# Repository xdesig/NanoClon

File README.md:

# NanoClon V 0.01   

## initial version.
Circuit that has everything you need to assemble your mClon-style robot, 
avoiding having to look for the missing Arduino one from RobotDyn that 
was used in the ShieldClon version.

The components can be SMD or THT, except for the Step-Up circuit/Lipo 
battery charge controller which is SMD,  with 1206 and 0805 components
larger than the usual 0603 and 0402).
You can an option not solder the smd components of the step-up,
and use a power bank by simply soldering the Bat-Vcc selector on the underside.

### [Assembly manual][Man]

#### Deseñado en Estrimia con agarimo.

## Author and license
* Author: [XDeSIG][TWI01]
* License:[CERN Open Hardware Licence Version 2 - Weakly Reciprocal][CERN-OHL-W]

## To buy boards

Developer don't produce boards to sell. Under [_provider_][provider]
directory there are instructions to order yourself.

<!-- links -->
[Man]: https://github.com/xdesig/NanoClon/blob/main/docs/nClon_001_Montaxe.pdf
[tecnoloxia.org]: https://tecnoloxia.org/mclon/que-e-mclon/
[CERN-OHL-W]: https://ohwr.org/cern_ohl_w_v2.pdf
[TWI01]: https://twitter.com/xdesig
[provider]: https://www.pcbway.com/project/shareproject/W50475ASJ144_NanoClon_001_gerber_f511f448.html

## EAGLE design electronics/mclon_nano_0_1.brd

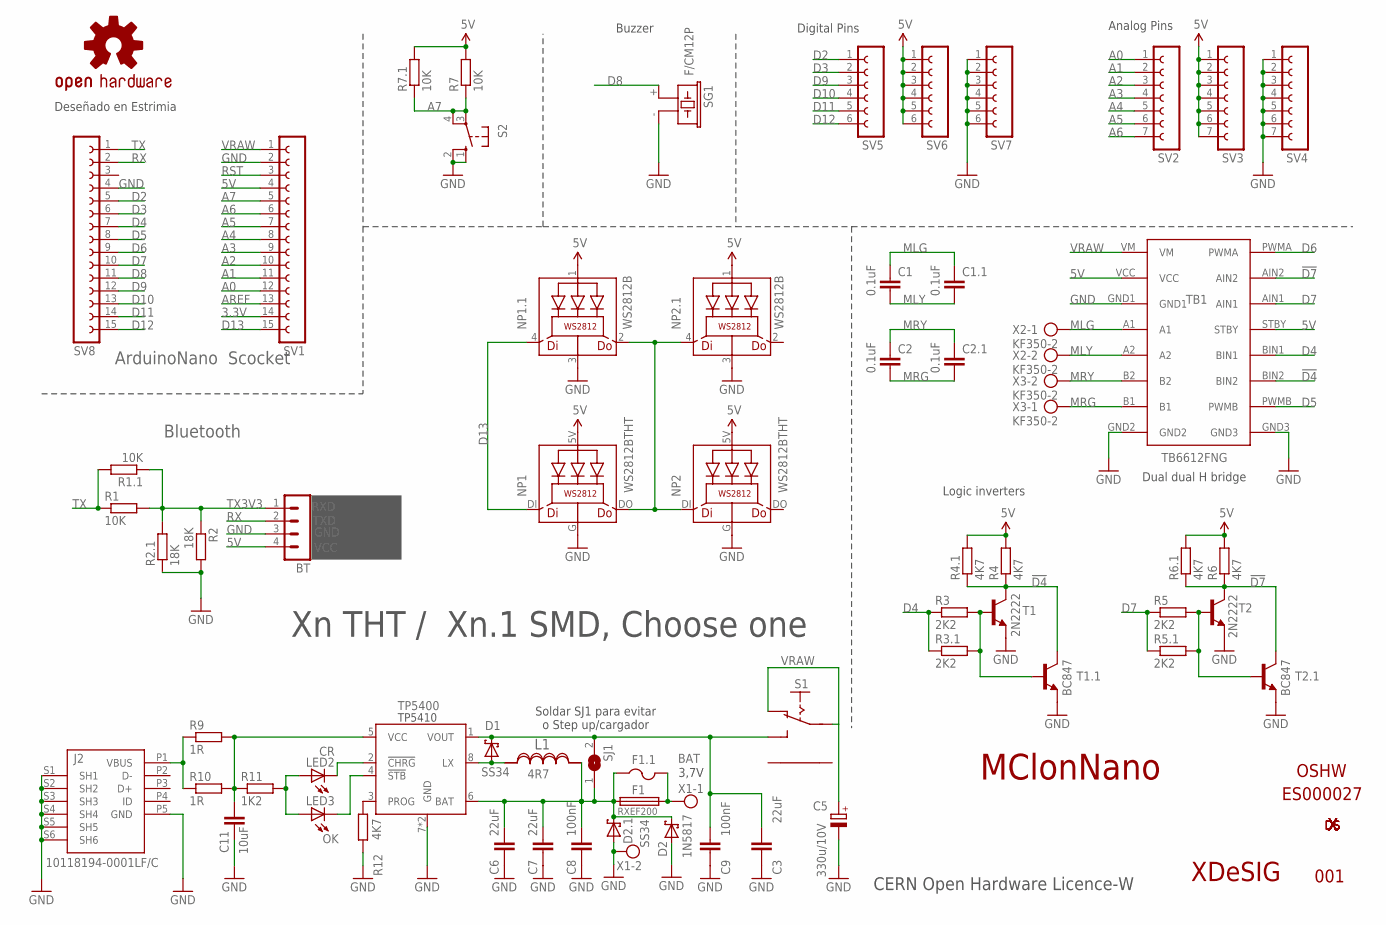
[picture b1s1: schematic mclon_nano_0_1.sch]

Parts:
BT: MA04-1
C1, C2: 0.1uF; C050-024X044
C1.1, C2.1: 0.1uF; C1206
C3, C6, C7: 22uF; C1206
C5: 330u/10V; E2,5-6
C8, C9: 100nF; C1206
C11: 10uF; C1206
D1, D2.1: SS34; DIODE_SMA
D2: 1N5817; DO35-7
F1: RXEF200; TE5
F1.1: MF-NSMF200; 1812
J2: 10118194-0001LF/C; SMARTPRJ_CON2_USB_MICRO_B_AT
L1: 4R7; SRN6045
LED2: CR; CHIPLED_0805
LED3: OK; CHIPLED_0805
LOGO4: OSHW-LOGOS; OSHW-LOGO-S
NP1, NP2: WS2812BTHT; NEOPIXEL5MM
NP1.1, NP2.1: WS2812B; 5050-4
R1, R7: 10K; 0204/7
R1.1, R7.1: 10K; R1206
R2: 18K; 0204/7
R2.1: 18K; R1206
R3, R5: 2K2; 0204/7
R3.1, R5.1: 2K2; R1206
R4, R6: 4K7; 0204/7
R4.1, R6.1, R12: 4K7; R1206
R9, R10: 1R; M1206
R11: 1K2; R1206
S1: ESCORNA_SK12F14D; ESCORNA_SK-12D07
S2: 10-XX; B3F-10XX
SG1: F/CM12P
SJ1: JUMPER_SJW
SV1, SV8: CON-LSTA_FE15-1; CON-LSTA_FE15
SV2, SV3, SV4: FE07-1; FE07
SV5, SV6, SV7: FE06-1; FE06
T1, T2: 2N2222; TO92-EBC-OVAL
T1.1, T2.1: BC847; SOT23
TB1: TB6612FNG
U1: TP5400; ESOP8
U$7: OSHW
U$8, U$19: XDESIG5MM; XDESIG_CU
U$18: XDESIG21; XDESIG
X1, X2, X3: KF350-2; AK550/2

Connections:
3.3V: SV1.14
5V: BT.4, NP1.5V (LEDVDD), NP1.1.1 (LEDVDD), NP2.5V (LEDVDD), NP2.1.1 (LEDVDD), R4.2, R4.1.2, R6.2, R6.1.2, R7.2, R7.1.2, SV1.4, SV3.1, SV3.2, SV3.3, SV3.4, SV3.5, SV3.6, SV3.7, SV6.1, SV6.2, SV6.3, SV6.4, SV6.5, SV6.6, TB1.STBY, TB1.VCC
!D4: R4.1, R4.1.1, T1.C, T1.1.3 (C), TB1.BIN2
!D7: R6.1, R6.1.1, T2.C, T2.1.3 (C), TB1.AIN2
A0: SV1.12, SV2.1
A1: SV1.11, SV2.2
A2: SV1.10, SV2.3
A3: SV1.9, SV2.4
A4: SV1.8, SV2.5
A5: SV1.7, SV2.6
A6: SV1.6, SV2.7
A7: R7.1, R7.1.1, S2.3, S2.4 (P1), SV1.5
AREF: SV1.13
BAT: C6.1, C7.1, C8.1, D2.C, D2.1.C, F1.1, F1.1.1, L1.1, SJ1.1, U1.6 (BAT)
D2: SV5.1, SV8.5
D3: SV5.2, SV8.6
D4: R3.1, R3.1.1, SV8.7, TB1.BIN1
D5: SV8.8, TB1.PWMB
D6: SV8.9, TB1.PWMA
D7: R5.1, R5.1.1, SV8.10, TB1.AIN1
D8: SG1.+ (1), SV8.11
D9: SV5.3, SV8.12
D10: SV5.4, SV8.13
D11: SV5.5, SV8.14
D12: SV5.6, SV8.15
D13: NP1.DI, NP1.1.4 (DI), SV1.15
GND: BT.3, C3.2, C5.-, C6.2, C7.2, C8.2, C9.2, C11.2, D2.A, D2.1.A, J2.P5 (GND), J2.S1 (SH1), J2.S2 (SH2), J2.S3 (SH3), J2.S4 (SH4), J2.S5 (SH5), J2.S6 (SH6), NP1.G (GND), NP1.1.3 (GND), NP2.G (GND), NP2.1.3 (GND), R2.2, R2.1.1, R12.1, S2.1 (S), S2.2 (S1), SG1.- (2), SV1.2, SV4.1, SV4.2, SV4.3, SV4.4, SV4.5, SV4.6, SV4.7, SV7.1, SV7.2, SV7.3, SV7.4, SV7.5, SV7.6, SV8.4, T1.E, T1.1.2 (E), T2.E, T2.1.2 (E), TB1.GND1, TB1.GND2, TB1.GND3, U1.7 (GND), U1.9 (GND), X1.2
MLG: C1.1, C1.1.1, TB1.A1, X2.1
MLY: C1.2, C1.1.2, TB1.A2, X2.2
MRG: C2.2, C2.1.2, TB1.B1, X3.1
MRY: C2.1, C2.1.1, TB1.B2, X3.2
unnamed: R3.2, R3.1.2, T1.B, T1.1.1 (B)
unnamed: F1.2, F1.1.2, X1.1
unnamed: R5.2, R5.1.2, T2.B, T2.1.1 (B)
unnamed: LED2.A, LED3.A, R11.2
unnamed: LED2.C, U1.2 (!CHRG)
unnamed: NP1.DO, NP1.1.2 (DO), NP2.DI, NP2.1.4 (DI)
unnamed: D1.A, L1.2, U1.8 (LX)
unnamed: LED3.C, U1.4 (!STB)
unnamed: R12.2, U1.3 (PROG)
RST: SV1.3
RX: BT.2, SV8.2
TX: R1.1, R1.1.2, SV8.1
TX3V3: BT.1, R1.2, R1.1.1, R2.1, R2.1.2
VBUS: J2.P1 (VBUS), R9.1, R10.1
VCC: C3.1, C9.1, D1.C, S1.P$3 (S), SJ1.2, U1.1 (VOUT)
VCH: C11.1, R9.2, R10.2, R11.1, U1.5 (VCC)
VRAW: C5.+, S1.P$1, S1.P$2 (O), SV1.1, TB1.VM

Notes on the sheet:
MClonNano
001
Bluetooth
RXD
TXD
GND
VCC
XDeSIG
Digital Pins
Analog Pins
Dual dual H bridge
Logic inverters
Deseñado en Estrimia
ArduinoNano Scocket
3,7V
Soldar SJ1 para evitar o Step up/cargador
TP5400
CERN Open Hardware Licence-W
Buzzer
Xn THT / Xn.1 SMD, Choose one
TP5410
ES000027

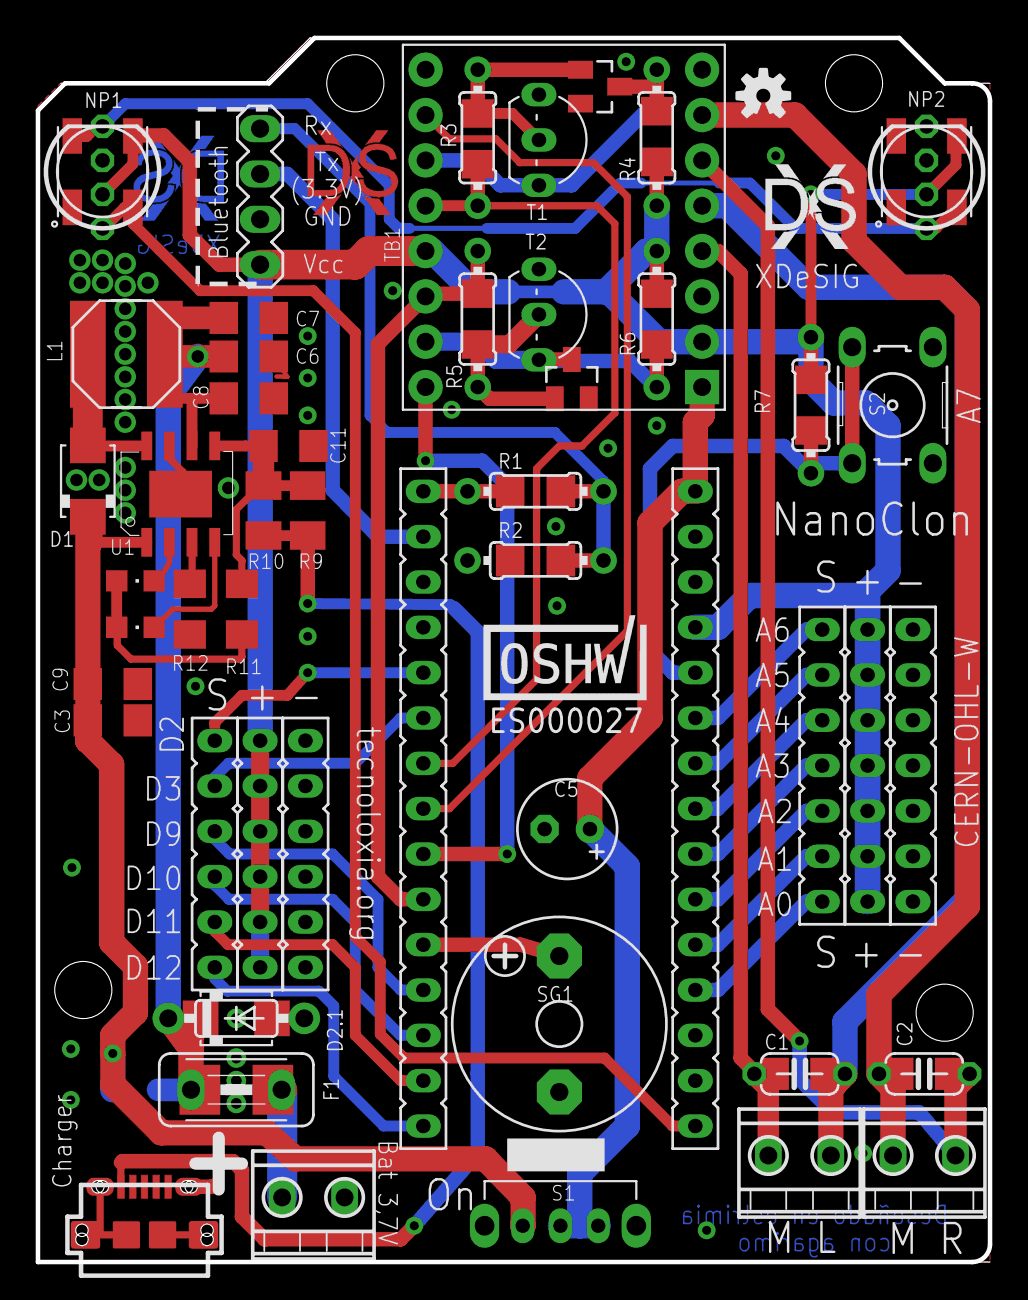
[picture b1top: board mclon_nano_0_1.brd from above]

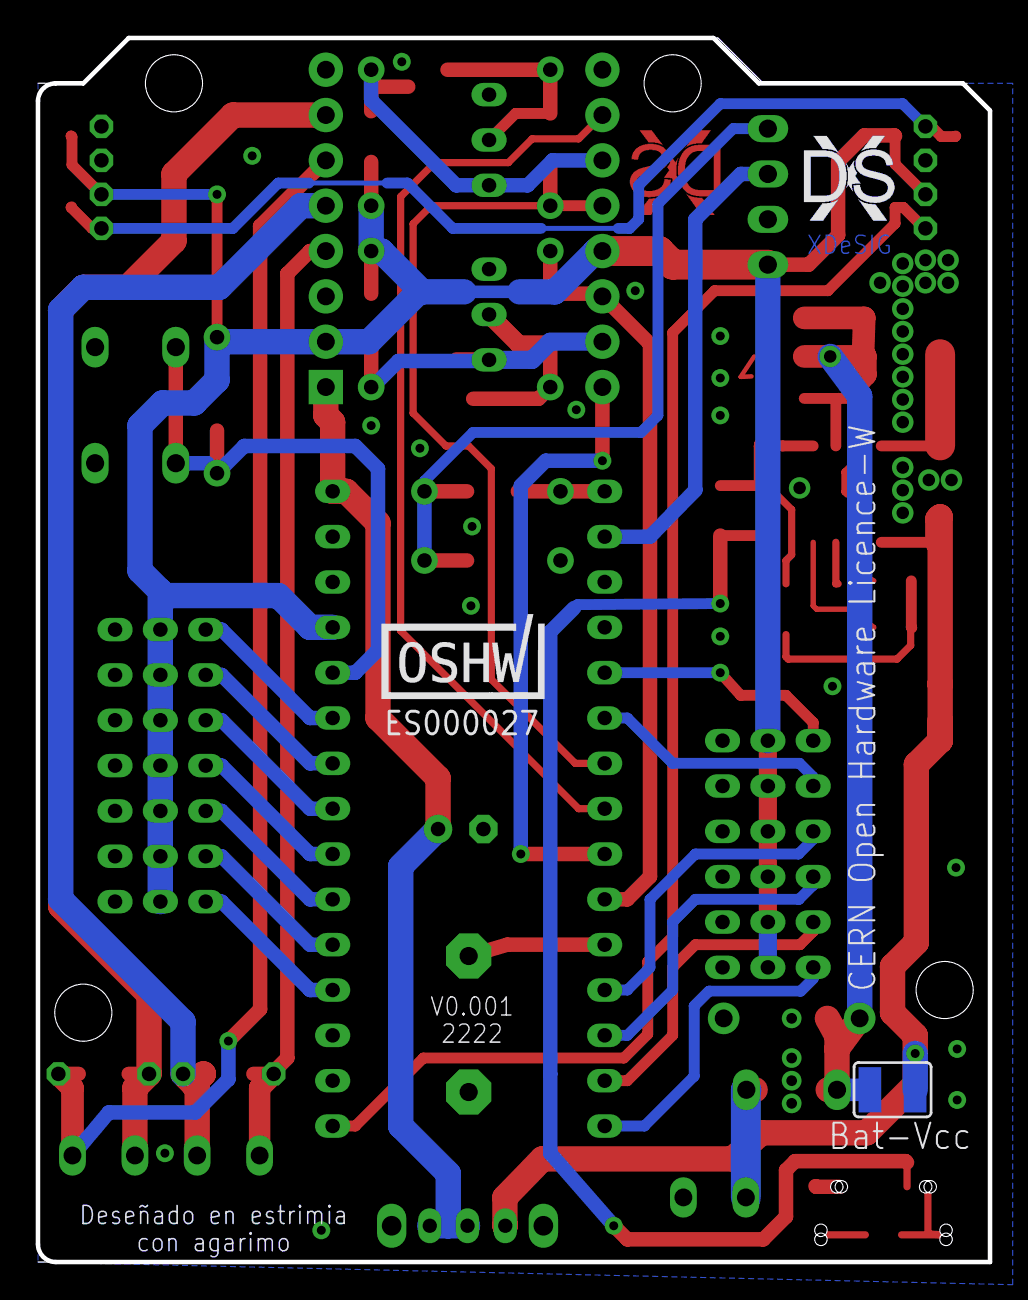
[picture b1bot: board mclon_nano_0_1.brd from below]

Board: 2 copper layers, 53.3 x 68.6 mm, 71 parts (4 on the bottom side), 45 nets.

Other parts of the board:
U$2: OSHW
U$21: XDESIG21; XDESIG

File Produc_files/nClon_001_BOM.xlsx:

Qty | Value | Parts | Device | Package | LCSC | Others | Notes
THT
1 |  | S2 | 10-XX | B3F-1000 | TS665CJ
2 |  | SV1, SV8 | CON-LSTA_FE15-1 | CON-LSTA_FE15 | C124408
1 |  | S1 | SK12F14 | SK12F14G5 | SK12F14G5
3 |  | SV5, SV6, SV7 | FE06-1 | FE06 | C37208 |  | SV5 White, SV6 Reed, SV7 Black
3 |  | SV2, SV3, SV4 | FE07-1 | FE07 | DZ254R-11-0 | # | SV2 White, SV3 Reed, SV4 Black
1 |  | BT | MA04-1 | MA04-1 | C2718488
1 | 1N5817 | D2 | DIODE_SCHOTTKY | DO35-7 | 1N5817
2 | 0.1uF | C1, C2 | 100nF/50V 5mm | C050-024X044 | C2896059
1 | 330u/10V | C5 | CPOL-EUE2.5-6 | E2,5-6 | C399138
2 | 4K7 | R4, R6 | R-EU_0204/7 | 0204/7 | C119339
2 | 10K | R1, R7 | 10K/0,25W | 0204/7 | C172967
1 | 18K | R2 | 18K/0,25W | 0204/7 | C410668
2 | 2K2 | R3, R5 | R-EU_0204/7 | 0204/7 | C714002
2 | 2N2222 | T1, T2 | 2N2222 | TO92-EBC-OVAL | C118536
3 | KF350-2 | X1, X2, X3 | KF350-2 | KF350-2 | C474892
1 | F/CM12P | SG1 | F/CM12Pasive | 12mm | C252921 |  | Magnetic 2.5V~5V 3.6V 2048Hz
1 | RXEF200 | F1 | FUSETE5 | 5,1mm / 6,2mm Ih > 500mA | C506879
1 | TB6612FNG | TB1 | TB6612FNG | TB6612FNG | # | TB6612FNG | Driver Motor
2 | WS2812BTHT | NP1, NP2 | WS2812BTHT | NEOPIXEL5MM | # | WS2812BTHT | Neo Pixel
1 | Nano | # | Arduino Nano | 2 x 15 | # | Arduino Nano
SMD
4 | 0.1uF | C1.1, C2.1, C8, C9 | C-EUC1206 | C1206 | C2443212
3 | 22uF | C3, C6, C7 | C-EUC1206 | C1206 | C2342487
1 | 10uF | C11 | C-EUC1206 | C1206 | C2174589
1 | 10118194-0001LF/C | J2 | MicroXNJ_USB | Micro-B SMD | C404969
2 | 10K | R1.1, R7.1 | R-EU_R1206 | R1206 | C2479071
1 | 18K | R2.1 | R-EU_R1206 | R1206 | C2595352
1 | 1K2 | R11 | R-EU_R1206 | R1206 | C2595146
2 | 1R | R9, R10 | R-EU_M1206 | M1206 | C237145
2 | 2K2 | R3.1, R5.1 | R-EU_R1206 | R1206 | C2481712
3 | 4K7 | R4.1, R6.1, R12 | R-EU_R1206 | R1206 | C2481314
1 | 4R7 | L1 | SRN6045-330M6045 | SRN6045 | C439386 |  | 4.7uH ±30%
1 | CR | LED2 | LED_REED | LED_0805 | C965812
1 | OK | LED3 | LED_GREN | LED_0805 | C965816
1 | MF-NSMF200 | F1.1 | PTCFUSE | 1812/1206 | C89656
2 | SS34 | D1, D2.1 | DIODE_SCHOTTKY | DIODE_SMA | C478723
2 | BC847 | T1.1, T2.1 | BC847 | SOT23 | C509816 | BC847C – 1G
1 | TP5400 | U1 | TP5400 | ESOP8 | C24154
2 | WS2812B | NP1.1, NP2.1 | WS2812B | 5050-4 | C2843785

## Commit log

2022-05-21 Initial
2022-05-21 rename
2022-06-04 Update img
2022-06-16 update gerber
2022-08-01 Renumber
2022-08-01 Update img.
2022-08-05 Create LICENSE
2023-01-12 Update components link
2023-01-12 Updating missing component links
2025-03-07 User update

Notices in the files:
electronics/mclon_nano_0_1.brd:
Attribution-ShareAlike 4.0 International (CC BY-SA 4.0)  XDeSIG
parts and their libraries:
SparkFun-Aesthetics: Licensing: CC v3.0 Share-Alike You are welcome to use this library for commercial purposes.
